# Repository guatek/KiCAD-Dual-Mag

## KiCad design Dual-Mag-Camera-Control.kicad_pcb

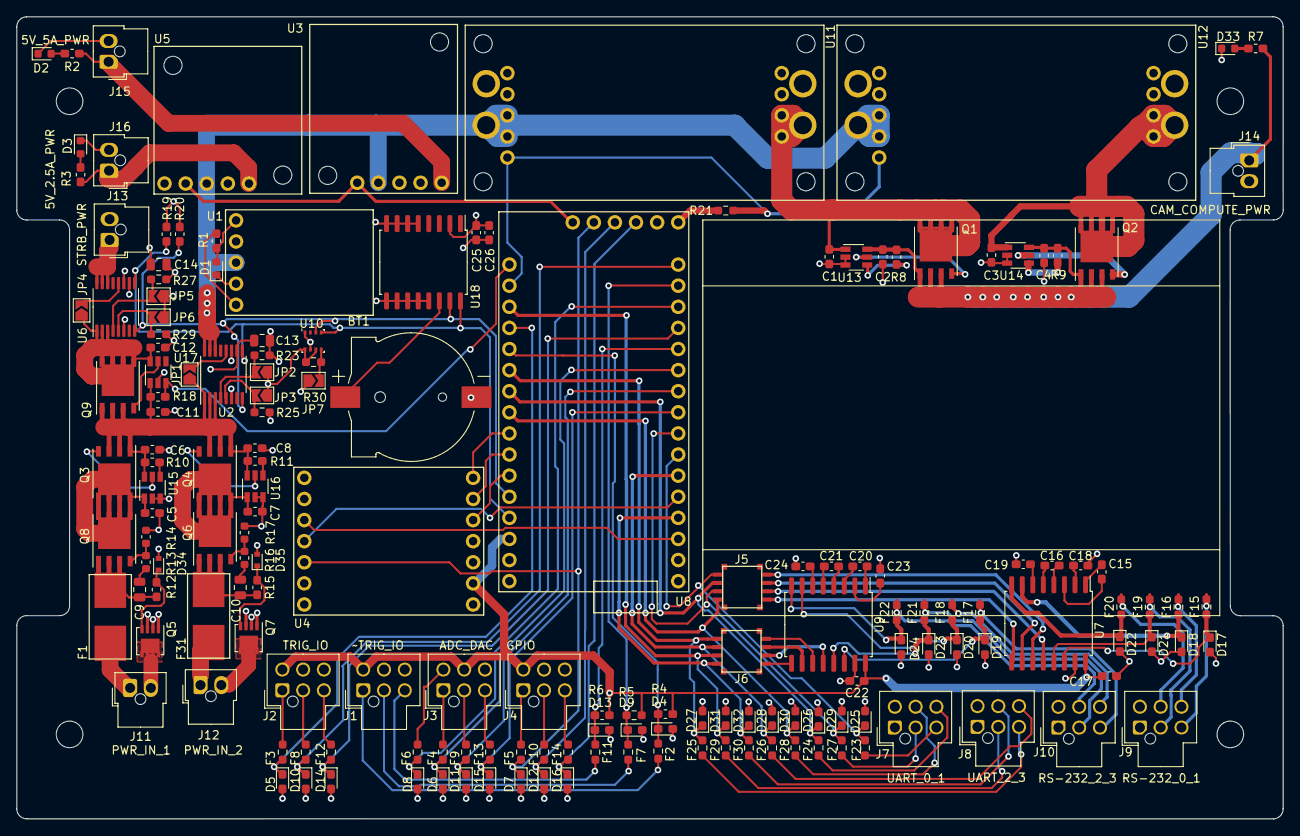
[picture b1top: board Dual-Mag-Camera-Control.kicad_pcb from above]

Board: 4 copper layers, 152.4 x 96.5 mm, 169 parts (0 on the bottom side), 135 nets.

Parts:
BT1: 1056; BAT_1056
C1, C2, C3, C4, C5, C6, C7, C8, C11, C12: 0.1 uF 50V; C_0603_1608Metric_Pad1.05x0.95mm_HandSolder
C9, C10, C13, C14: 1 uF; C_0805_2012Metric
C15, C16, C17, C18, C19, C20, C21, C22, C23, C24, C25: 0.1 uF 50V; C_0603_1608Metric_Pad1.08x0.95mm_HandSolder
C26: 10 uF 50V; C_0603_1608Metric_Pad1.08x0.95mm_HandSolder
D1: GRN 1.7V@1mA; LED_0603_1608Metric
D2, D3, D33: ORG 1.8V@1mA; LED_0603_1608Metric
D4, D5, D6, D7, D8, D9, D10, D11, D12, D13, D14, D15, D16, D25, D26, D27, D28, D29, D30, D31, D32: CZRU52C3V3; D_0603_1608Metric_Pad1.05x0.95mm_HandSolder
D17, D18, D19, D20, D21, D22, D23, D24: CZRU52C15; D_0603_1608Metric_Pad1.05x0.95mm_HandSolder
D34, D35: BZT52C20T-7; D_SOD-523
F1, F31: 01550900M(Holder); 01550900M
F2, F3, F4, F5, F6, F7, F8, F9, F10, F11, F12, F13, F14, F15, F16, F17, F18, F19, F20, F21, F22, F23, F24, F25, F26, F27, F28, F29, F30: PTC; R_0603_1608Metric_Pad0.98x0.95mm_HandSolder
J1: ~TRIG_IO; Molex_Nano-Fit_105310-xx06_2x03_P2.50mm_Vertical
J2: TRIG_IO; Molex_Nano-Fit_105310-xx06_2x03_P2.50mm_Vertical
J3: ADC_DAC; Molex_Nano-Fit_105310-xx06_2x03_P2.50mm_Vertical
J4: GPIO; Molex_Nano-Fit_105310-xx06_2x03_P2.50mm_Vertical
J5, J6: CVS-04TB
J7: UART_0_1; Molex_Nano-Fit_105310-xx06_2x03_P2.50mm_Vertical
J8: UART_2_3; Molex_Nano-Fit_105310-xx06_2x03_P2.50mm_Vertical
J9: RS-232_0_1; Molex_Nano-Fit_105310-xx06_2x03_P2.50mm_Vertical
J10: RS-232_2_3; Molex_Nano-Fit_105310-xx06_2x03_P2.50mm_Vertical
J11: PWR_IN_1; Molex_Nano-Fit_105309-xx02_1x02_P2.50mm_Vertical
J12: PWR_IN_2; Molex_Nano-Fit_105309-xx02_1x02_P2.50mm_Vertical
J13: STRB_PWR; Molex_Nano-Fit_105309-xx02_1x02_P2.50mm_Vertical
J14: CAM_COMPUTE_PWR; Molex_Nano-Fit_105309-xx02_1x02_P2.50mm_Vertical
J15: 5V_5A_PWR; Molex_Nano-Fit_105309-xx02_1x02_P2.50mm_Vertical
J16: 5V_2.5A_PWR; Molex_Nano-Fit_105309-xx02_1x02_P2.50mm_Vertical
JP1, JP2, JP3, JP4, JP5, JP6, JP7: SolderJumper_2_Open; SolderJumper-2_P1.3mm_Open_TrianglePad1.0x1.5mm
Q1, Q2, Q3, Q4, Q6, Q8, Q9: Si7463DP; PowerPAK_SO-8_Single
Q5, Q7: SISS12DN; Vishay_PowerPAK_1212-8_Single
R1, R2, R3: 3240; R_0603_1608Metric_Pad1.05x0.95mm_HandSolder
R4, R6: 1k; R_0603_1608Metric_Pad1.05x0.95mm_HandSolder
R5: 1k; R_0603_1608Metric_Pad0.98x0.95mm_HandSolder
R7: 10.2k; R_0603_1608Metric_Pad1.05x0.95mm_HandSolder
R8, R9, R10, R11, R18: 470k; R_0603_1608Metric_Pad1.05x0.95mm_HandSolder
R12, R15, R19, R20: 10K; R_0603_1608Metric_Pad1.05x0.95mm_HandSolder
R13, R16: 100; R_0603_1608Metric
R14, R17: 499k; R_0603_1608Metric
R21: 20k; R_0603_1608Metric_Pad0.98x0.95mm_HandSolder
R23, R25, R27, R29, R30: 10K; R_0603_1608Metric_Pad0.98x0.95mm_HandSolder
U1: D24V10F5
U2, U6: INA260; TSSOP-16_4.4x5mm_P0.65mm
U3: D24V50F5
U4: LowPowerLab-SD-Card; LowPowerLabs-SD-Card
U5: D24V22F5
U7, U9: SOIC-16W_7.5x10.3mm_P1.27mm
U8: MoteinoM0
U10: BME280; Bosch_LGA-8_2.5x2.5mm_P0.65mm_ClockwisePinNumbering
U11, U12: S18V20F12; S18V20x
U13, U14, U15, U16, U17: LTC4412HVIS6; TSOT-23-6
U18: DS3231M; SOIC-16W_7.5x10.3mm_P1.27mm

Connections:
/3.3V_LDO: C13.1, C14.1, C17.1, C22.1, C25.1, C26.1, J1.4, J2.4, J3.5, J4.4, JP2.1 (A), JP3.1 (A), JP5.1 (A), JP6.1 (A), R4.2, R5.2, R6.2, R19.1, R20.1, R30.1, U2.10 (VS), U4.2 (3V), U6.10 (VS), U7.16 (VCC), U8.30 (3.3V_LDO), U8.34 (3.3V_LDO), U9.16 (VCC), U10.6 (VDDIO), U10.8 (VDD), U18.2 (VCC)
/5V_2.5A_OUT: J16.1, R3.2, U5.1 (Vout)
/5V_5A_OUT: J15.1, R2.2, U3.1 (Out)
/5V_reg: J1.5, J2.5, J4.5, R1.1, U1.5 (Vout), U8.32 (Vin_(3.6V-6V))
/A3: D6.1, F4.1, U8.11 (A3(PA04(AIN4/REFB/SER0:0/TC0:0)))
/A3_IO: F4.2, J3.1
/A4: D11.1, F9.1, U8.10 (A4(PA05(AIN5/SER0:1/TC0:1)))
/A4_IO: F9.2, J3.2
/A5: D15.1, F13.1, U8.9 (A5(PB02(AIN10/SER5:0))
/A5_IO: F13.2, J3.3
/Adafruit_BME280/SDO/ADR: JP7.2 (B), R30.2, U10.5 (SDO)
/Adafruit_INA260/VBUS: JP1.2 (B), U2.12 (VBUS)
/Adafruit_INA260/Vin+: C6.1, C8.1, C11.1, JP1.1 (A), Q3.1 (S), Q3.2 (S), Q3.3 (S), Q4.1 (S), Q4.2 (S), Q4.3 (S), Q9.1 (S), Q9.2 (S), Q9.3 (S), R10.1, R11.1, R18.1, U2.1 (IN+), U2.2 (IN+), U2.3 (IN+), U15.6 (SENSE), U16.6 (SENSE), U17.1 (VIN)
/Adafruit_INA260_1/VBUS: JP4.2 (B), U6.12 (VBUS)
/Adafruit_INA260_1/Vin+: C12.1, JP4.1 (A), Q9.5 (D), U6.1 (IN+), U6.2 (IN+), U6.3 (IN+), U17.6 (SENSE)
/COMMS/RX0: D21.1, F19.1, U7.13 (R1IN)
/COMMS/RX0_OUT: F19.2, J9.2
/COMMS/RX1: D22.1, F20.1, U7.8 (R2IN)
/COMMS/RX1_OUT: F20.2, J9.5
/COMMS/RX2: D23.1, F21.1, U9.13 (R1IN)
/COMMS/RX2_OUT: F21.2, J10.2
/COMMS/RX3: D24.1, F22.1, U9.8 (R2IN)
/COMMS/RX3_OUT: F22.2, J10.5
/COMMS/Sparkfun_MAX3232/R1_OUT: J5.6, U7.12 (R1OUT)
/COMMS/Sparkfun_MAX3232/R2_OUT: J5.5, U7.9 (R2OUT)
/COMMS/Sparkfun_MAX3232/T1_IN: J5.8, U7.11 (T1IN)
/COMMS/Sparkfun_MAX3232/T2_IN: J5.7, U7.10 (T2IN)
/COMMS/Sparkfun_MAX3233/R1_OUT: J6.6, U9.12 (R1OUT)
/COMMS/Sparkfun_MAX3233/R2_OUT: J6.5, U9.9 (R2OUT)
/COMMS/Sparkfun_MAX3233/T1_IN: J6.8, U9.11 (T1IN)
/COMMS/Sparkfun_MAX3233/T2_IN: J6.7, U9.10 (T2IN)
/COMMS/TX0: D17.1, F15.1, U7.14 (T1OUT)
/COMMS/TX0_OUT: F15.2, J9.3
/COMMS/TX1: D18.1, F16.1, U7.7 (T2OUT)
/COMMS/TX1_OUT: F16.2, J9.6
/COMMS/TX2: D19.1, F17.1, U9.14 (T1OUT)
/COMMS/TX2_OUT: F17.2, J10.3
/COMMS/TX3: D20.1, F18.1, U9.7 (T2OUT)
/COMMS/TX3_OUT: F18.2, J10.6
/COMMS/UART_RX0_OUT: F27.2, J7.2
/COMMS/UART_RX1_OUT: F28.2, J7.5
/COMMS/UART_RX2_OUT: F29.2, J8.2
/COMMS/UART_RX3_OUT: F30.2, J8.5
/COMMS/UART_TX0_OUT: F23.2, J7.3
/COMMS/UART_TX1_OUT: F24.2, J7.6
/COMMS/UART_TX2_OUT: F25.2, J8.3
/COMMS/UART_TX3_OUT: F26.2, J8.6
/CamVout: C2.1, C4.1, J14.1, Q1.1 (S), Q1.2 (S), Q1.3 (S), Q2.1 (S), Q2.2 (S), Q2.3 (S), R7.2, R8.1, R9.1, U13.6 (SENSE), U14.6 (SENSE)
/CameraPower/LTC4412HV/Vin: C1.1, Q1.5 (D), U11.4 (Vout), U13.1 (VIN)
/CameraPower/sheet5F4C3746/Vin: C3.1, Q2.5 (D), U12.4 (Vout), U14.1 (VIN)
/DAC_OUT: D8.1, F6.1, U8.14 (A0(PA02(AIN0/DAC)))
/DAC_OUT_IO: F6.2, J3.4
/GND: BT1.-, C1.2, C2.2, C3.2, C4.2, C5.2, C6.2, C7.2, C8.2, C11.2, C12.2, C13.2, C14.2, C17.2, C18.2, C19.2, C22.2, C23.2, C24.2, C25.2, C26.2, D1.1 (K), D2.1 (K), D3.1 (K), D4.2, D5.2, D6.2, D7.2, D8.2, D9.2, D10.2, D11.2, D12.2, D13.2, D14.2, D15.2, D16.2, D17.2, D18.2, D19.2, D20.2, D21.2, D22.2, D23.2, D24.2, D25.2, D26.2, D27.2, D28.2, D29.2, D30.2, D31.2, D32.2, D33.1 (K), D34.2 (A), D35.2 (A), J1.6, J2.6, J3.6, J4.6, J7.1, J7.4, J8.1, J8.4, J9.1, J9.4, J10.1, J10.4, J13.2, J14.2, J15.2, J16.2, JP7.1 (A), Q5.1 (S), Q5.2 (S), Q5.3 (S), Q7.1 (S), Q7.2 (S), Q7.3 (S), R14.2, R17.2, R21.2, R23.2, R25.2, R27.2, R29.2, U1.4 (GND), U2.6 (GND), U2.11 (GND), U3.2 (GND), U3.3 (GND), U4.1 (GND), U4.14 (GND), U5.2 (GND), U6.6 (GND), U6.11 (GND), U7.15 (GND), U8.2 (GND), U8.31 (GND), U8.33 (GND), U9.15 (GND), U10.1 (GND), U10.7 (GND), U11.1 (GND), U11.5 (GND), U12.1 (GND), U12.5 (GND), U13.2 (GND), U13.3 (CTL), U14.2 (GND), U14.3 (CTL), U15.2 (GND), U15.3 (CTL), U16.2 (GND), U16.3 (CTL), U17.2 (GND), U18.5 (GND), U18.6 (GND), U18.7 (GND), U18.8 (GND), U18.9 (GND), U18.10 (GND), U18.11 (GND), U18.12 (GND), U18.13 (GND)
/GPIO_1: D7.1, F5.1, U4.12 (CD), U8.37 (AREF(PA03(AIN1/REFA)))
/GPIO_1_IO: F5.2, J4.1
/GPIO_2: D12.1, F10.1, U8.36 (SWDIO(PA31(SWDIO/SER1:3+)))
/GPIO_2_IO: F10.2, J4.2
/GPIO_3: D16.1, F14.1, U8.35 (SWCLK(PA30(SWCLK/SER1:2+)))
/GPIO_3_IO: F14.2, J4.3
/PowerInput1/Vin: C5.1, Q3.5 (D), Q8.5 (D), U15.1 (VIN)
/PowerInput2/Vin: C7.1, Q4.5 (D), Q6.5 (D), U16.1 (VIN)
/PowerInputPreotection2/Vin: F31.1, J12.1
/PowerInputProtection/Vin: F1.1, J11.1
/SCL_1: R19.2, U2.9 (SCL), U6.9 (SCL), U8.29 (SCL(PA23(I2C/SER3:0+))), U10.4 (SCK), U18.16 (SCL)
/SDA_1: R20.2, U2.8 (SDA), U6.8 (SDA), U8.28 (SDA(PA22(I2C/SER3:0+))), U10.3 (SDI), U18.15 (SDA)
/SD_CS: U4.10 (CS), U8.3 (D13(PA17(I2C/SER1:1+)))
/SD_ENABLE: U4.11 (EN), U8.5 (D11(PA16(I2C/SER1:0+)))
/SPI_MISO: U4.5 (MI), U8.27 (SPI_MISO(PA12(I2C/SER2:0+)))
/SPI_MOSI: U4.7 (MO), U8.25 (SPI_MOSI(PB10(SER4:2+)))
/SPI_SCK: U4.6 (SCK), U8.26 (SPI_SCK(PB11(SER4:3+)))
/Serial0_RX: D29.1, F27.1, J5.3, U8.8 (D31(PB23(SER5:3+)))
/Serial0_TX: D25.1, F23.1, J5.1, U8.7 (D30(PB22(SER5:2+)))
/Serial1_RX: D30.1, F28.1, J5.4, U8.24 (D0(PA11(AIN19/SER0:3+)))
/Serial1_TX: D26.1, F24.1, J5.2, U8.23 (D1(PA10(AIN18/SER0:2+)))
/Serial2_RX: D31.1, F29.1, J6.3, U8.19 (D5(PA15(XOUT/SER2:3+)))
/Serial2_TX: D27.1, F25.1, J6.1, U8.22 (D2(PA14(XIN/SER2:2+)))
/Serial3_RX: D32.1, F30.1, J6.4, U8.4 (D12(PA19(SER1:3+)))
/Serial3_TX: D28.1, F26.1, J6.2, U8.6 (D10(PA18(SER1:2+)))
/StrobeVout: J13.1, U6.14 (IN-), U6.15 (IN-), U6.16 (IN-)
/SystemVin: U1.3 (Vin), U2.14 (IN-), U2.15 (IN-), U2.16 (IN-), U3.4 (Vin), U5.3 (Vin), U11.2 (Vin), U12.2 (Vin)
/TRIG0_0: D5.1, F3.1, U8.20 (D4(PA08(I2C/AIN16/SER0:0+)))
/TRIG0_0_IO: F3.2, J2.1
/TRIG0_1: D4.1, F2.1, R4.1, U8.21 (D3(PA09(I2C/AIN17/SER0:1+)))
/TRIG0_1_IO: F2.2, J1.1
/TRIG1_0: D10.1, F8.1, U8.16 (D8(PA06/AIN6/SER0:2/TC1:0))
/TRIG1_0_IO: F8.2, J2.2
/TRIG1_1: D9.1, F7.1, R5.1, U8.15 (D9(PA07/AIN7/SER0:3/TC1:1)))
/TRIG1_1_IO: F7.2, J1.2
/TRIG4_0: D14.1, F12.1, U8.13 (A1(PB08(AIN2/SER4:0/TC4:0)))
/TRIG4_0_IO: F12.2, J2.3
/TRIG4_1: D13.1, F11.1, R6.1, U8.12 (A2(PB09(AIN3/SER4:1/TC4:1)))
/TRIG4_1_IO: F11.2, J1.3
/uGnd1: J11.2, Q5.5 (D)
/uGnd2: J12.2, Q7.5 (D)
/~5V_ENABLE: U3.5 (EN), U5.4 (EN), U8.38 (ANT(PA13(I2C/SER2:1+)))
/~12V_ENABLE: R21.1, U8.18 (D6(PA20(SER5:2+))), U11.3 (ENABLE), U12.3 (ENABLE)
/~STROBE_ENABLE: R18.2, U8.17 (D7(PA21(SER5:3+))), U17.3 (CTL)
unnamed: BT1.+, U18.14 (VBAT)
unnamed: C9.1, F1.2, Q8.1 (S), Q8.2 (S), Q8.3 (S), R12.1
unnamed: C9.2, R13.2
unnamed: C10.1, F31.2, Q6.1 (S), Q6.2 (S), Q6.3 (S), R15.1
unnamed: C10.2, R16.2
unnamed: C15.1, U7.3 (C1-)
unnamed: C15.2, U7.1 (C1+)
unnamed: C16.1, U7.4 (C2+)
unnamed: C16.2, U7.5 (C2-)
unnamed: C18.1, U7.2 (VS+)
unnamed: C19.1, U7.6 (VS-)
unnamed: C20.1, U9.3 (C1-)
unnamed: C20.2, U9.1 (C1+)
unnamed: C21.1, U9.4 (C2+)
unnamed: C21.2, U9.5 (C2-)
unnamed: C23.1, U9.2 (VS+)
unnamed: C24.1, U9.6 (VS-)
unnamed: D1.2 (A), R1.2, U1.1 (PG)
unnamed: D2.2 (A), R2.1
unnamed: D3.2 (A), R3.1
unnamed: D33.2 (A), R7.1
unnamed: D34.1 (K), Q5.4 (G), R12.2
unnamed: D35.1 (K), Q7.4 (G), R15.2
unnamed: JP2.2 (B), R23.1, U2.4 (A1)
unnamed: JP3.2 (B), R25.1, U2.5 (A0)
unnamed: JP5.2 (B), R27.1, U6.4 (A1)
unnamed: JP6.2 (B), R29.1, U6.5 (A0)
unnamed: Q1.4 (G), U13.5 (GATE)
unnamed: Q2.4 (G), U14.5 (GATE)
unnamed: Q3.4 (G), U15.5 (GATE)
unnamed: Q4.4 (G), U16.5 (GATE)
unnamed: Q6.4 (G), R16.1, R17.1
unnamed: Q8.4 (G), R13.1, R14.1
unnamed: Q9.4 (G), U17.5 (GATE)
unnamed: R8.2, U13.4 (STAT)
unnamed: R9.2, U14.4 (STAT)
unnamed: R10.2, U15.4 (STAT)
unnamed: R11.2, U16.4 (STAT)

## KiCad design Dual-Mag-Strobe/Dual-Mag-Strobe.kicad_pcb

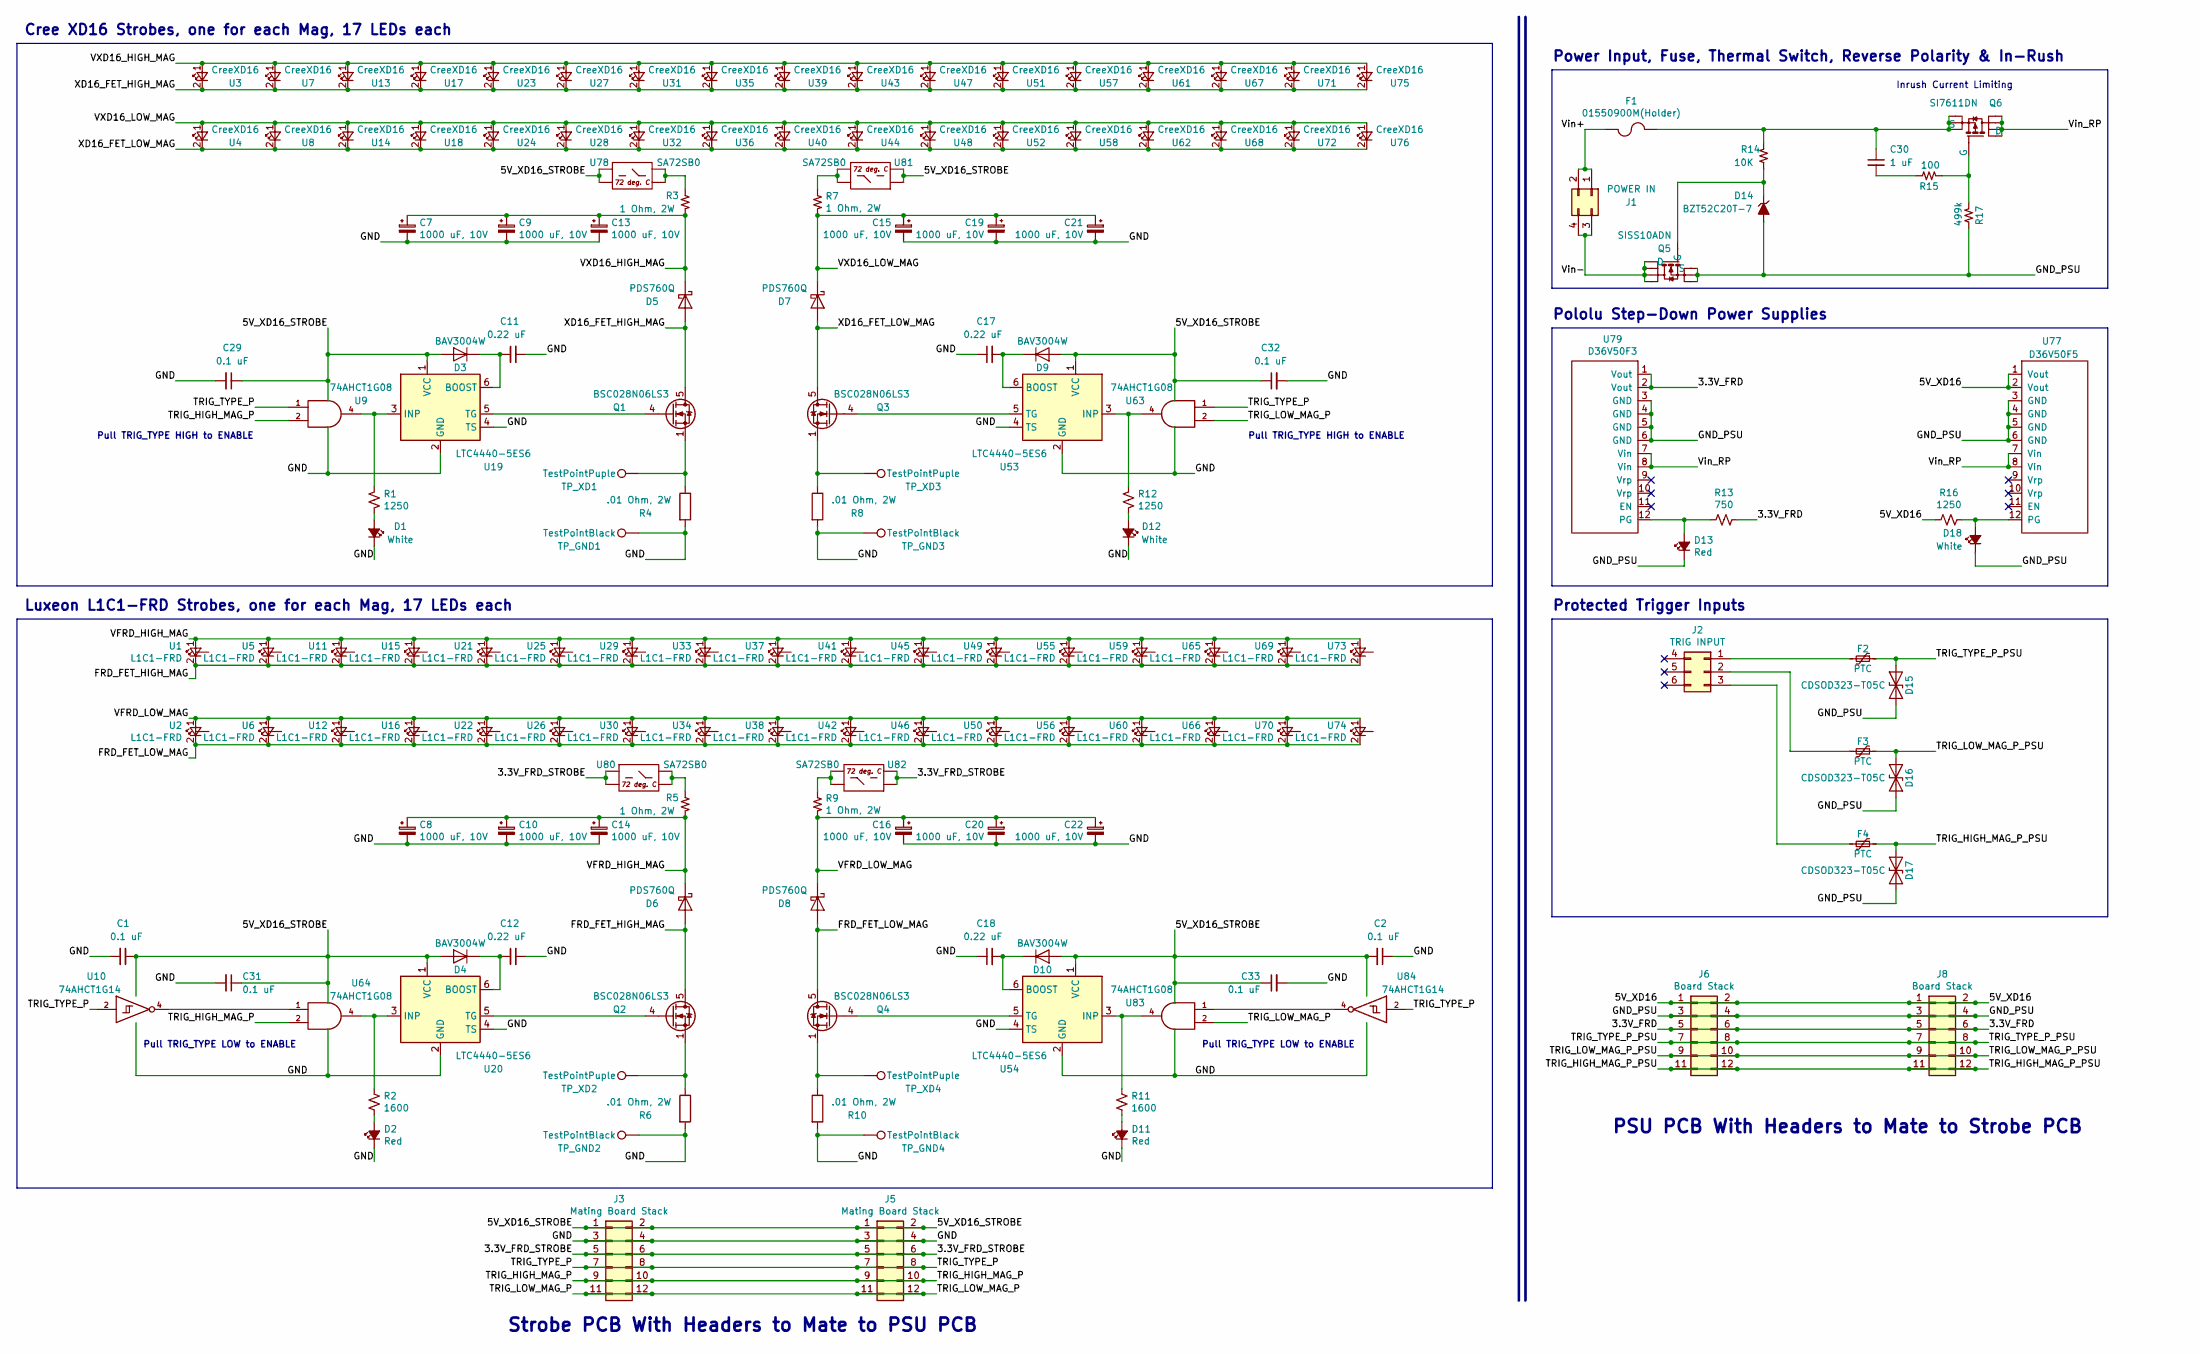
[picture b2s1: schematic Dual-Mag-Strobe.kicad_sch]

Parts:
C1, C2, C29, C31, C32, C33: 0.1 uF; C_0603_1608Metric; Part Number 399-7845-1-ND
C7, C8, C9, C10, C13, C14, C15, C16, C19, C20, C21, C22: 1000 uF, 10V; CP_EIA-7360-38_Kemet-E; Part Number 399-18694-1-ND
C11, C12, C17, C18: 0.22 uF; C_0603_1608Metric; Part Number 490-14410-1-ND
C30: 1 uF; C_0805_2012Metric; Part Number 311-3498-1-ND
D1, D12, D18: White; LED_0603_1608Metric; Part Number 1080-1574-1-ND
D2, D11, D13: Red; LED_0603_1608Metric; Part Number 475-2506-1-ND
D3, D4, D9, D10: BAV3004W; D_SOD-123; Part Number BAV3004W-FDICT-ND
D5, D6, D7, D8: PDS760Q; D_PowerDI-5; Part Number PDS760Q-13DICT-ND
D14: BZT52C20T-7; D_SOD-523; Part Number BZT52C20T-7
D15, D16, D17: CDSOD323-T05C; D_SOD-323; Part Number CDSOD323-T05CCT-ND
F1: 01550900M(Holder); 01550900M; Part Number F1889-ND
F2, F3, F4: PTC; R_1210_3225Metric; Part Number 495-3878-1-ND
J1: POWER IN; Molex_Nano-Fit_105310-xx04_2x02_P2.50mm_Vertical; Part Number WM15166-ND
J2: TRIG INPUT; Molex_Nano-Fit_105310-xx06_2x03_P2.50mm_Vertical; Part Number WM15076-ND
J3, J5: Mating Board Stack; PinSocket_2x06_P2.54mm_Vertical; Part Number SAM1092-06-ND
J6, J8: Board Stack; PinHeader_2x06_P2.54mm_Vertical; Part Number SAM1022-06-ND
Q1, Q2, Q3, Q4: BSC028N06LS3; TDSON-8-1; Part Number BSC028N06LS3GATMA1CT-ND
Q5: SISS10ADN; Vishay_PowerPAK_1212-8_Single; Part Number SISS10ADN-T1-GE3
Q6: SI7611DN; Vishay_PowerPAK_1212-8_Single; Part Number SI7611DN-T1-GE3
R1, R12, R16: 1250; R_0603_1608Metric; Part Number P1.27KHCT-ND
R2, R11: 1600; R_0603_1608Metric; Part Number P1.60KHCT-ND
R3, R5, R7, R9: 1 Ohm, 2W; R_2512_6332Metric; Part Number CRM2512-FX-1R00ELFCT-ND
R4, R6, R8, R10: .01 Ohm, 2W; R_2512_6332Metric; Part Number RHM.010AUCT-ND
R13: 750; R_0603_1608Metric; Part Number P750BYCT-ND
R14: 10K; R_0603_1608Metric_Pad1.05x0.95mm_HandSolder; Part Number MCT0603-10.0K-CFCT-ND
R15: 100; R_0603_1608Metric; Part Number P100DBCT-ND
R17: 499k; R_0603_1608Metric; Part Number YAG4565CT-ND
TP_GND1, TP_GND2, TP_GND3, TP_GND4: TestPointBlack; TestPoint_519xTR; Part Number 36-5191CT-ND
TP_XD1, TP_XD2, TP_XD3, TP_XD4: TestPointPuple; TestPoint_519xTR; Part Number 36-5199CT-ND
U1, U2, U5, U6, U11, U12, U15, U16, U21, U22, U25, U26, U29, U30, U33, U34, U37, U38, U41, U42, U45, U46, U49, U50, U55, U56, U59, U60, U65, U66, U69, U70, U73, U74: L1C1-FRD; Luxeon-L1C1-FRD; Part Number 997-L1C1-FRD10000000
U3, U4, U7, U8, U13, U14, U17, U18, U23, U24, U27, U28, U31, U32, U35, U36, U39, U40, U43, U44, U47, U48, U51, U52, U57, U58, U61, U62, U67, U68, U71, U72, U75, U76: CreeXD16; Cree_XD16_Min; Part Number 941-XD16AWTH000KE4
U9, U63, U64, U83: 74AHCT1G08; SOT-23-5; Part Number 296-1113-1-ND
U10, U84: 74AHCT1G14; SOT-23-5; Part Number 296-1112-1-ND
U19, U20, U53, U54: LTC4440-5ES6; SOT-23-6
U77: D36V50F5; D36V50Fx; Part Number 2183-4091-ND
U78, U80, U81, U82: SA72SB0; Part Number SA72SB0CT-ND
U79: D36V50F3; D36V50Fx; Part Number 2183-4090-ND

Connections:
/3.3V_FRD: J6.5, J6.6, J8.5, J8.6, R13.2, U79.1 (Vout), U79.2 (Vout)
/3.3V_FRD_STROBE: J3.5, J3.6, J5.5, J5.6, U80.1, U80.2, U82.1, U82.2
/5V_XD16: J6.1, J6.2, J8.1, J8.2, R16.1, U77.1 (Vout), U77.2 (Vout)
/FRD_FET_HIGH_MAG: D6.2 (A), Q2.5 (D), U1.2 (K), U5.2 (K), U11.2 (K), U15.2 (K), U21.2 (K), U25.2 (K), U29.2 (K), U33.2 (K), U37.2 (K), U41.2 (K), U45.2 (K), U49.2 (K), U55.2 (K), U59.2 (K), U65.2 (K), U69.2 (K), U73.2 (K)
/FRD_FET_LOW_MAG: D8.2 (A), Q4.5 (D), U2.2 (K), U6.2 (K), U12.2 (K), U16.2 (K), U22.2 (K), U26.2 (K), U30.2 (K), U34.2 (K), U38.2 (K), U42.2 (K), U46.2 (K), U50.2 (K), U56.2 (K), U60.2 (K), U66.2 (K), U70.2 (K), U74.2 (K)
/GND_PSU: D13.1 (K), D14.2 (A), D15.2 (A2), D16.2 (A2), D17.2 (A2), D18.1 (K), J6.3, J6.4, J8.3, J8.4, Q5.1 (S), Q5.2 (S), Q5.3 (S), R17.2, U77.3 (GND), U77.4 (GND), U77.5 (GND), U77.6 (GND), U79.3 (GND), U79.4 (GND), U79.5 (GND), U79.6 (GND)
/TRIG_HIGH_MAG_P: J3.9, J3.10, J5.9, J5.10, U9.2, U64.2
/TRIG_HIGH_MAG_P_PSU: D17.1 (A1), F4.1, J6.11, J6.12, J8.11, J8.12
/TRIG_LOW_MAG_P: J3.11, J3.12, J5.11, J5.12, U63.2, U83.2
/TRIG_LOW_MAG_P_PSU: D16.1 (A1), F3.1, J6.9, J6.10, J8.9, J8.10
/TRIG_TYPE_P: J3.7, J3.8, J5.7, J5.8, U9.1, U10.2, U63.1, U84.2
/TRIG_TYPE_P_PSU: D15.1 (A1), F2.1, J6.7, J6.8, J8.7, J8.8
/VFRD_HIGH_MAG: C8.1, C10.1, C14.1, D6.1 (K), R5.1, U1.1 (A), U5.1 (A), U11.1 (A), U15.1 (A), U21.1 (A), U25.1 (A), U29.1 (A), U33.1 (A), U37.1 (A), U41.1 (A), U45.1 (A), U49.1 (A), U55.1 (A), U59.1 (A), U65.1 (A), U69.1 (A), U73.1 (A)
/VFRD_LOW_MAG: C16.1, C20.1, C22.1, D8.1 (K), R9.1, U2.1 (A), U6.1 (A), U12.1 (A), U16.1 (A), U22.1 (A), U26.1 (A), U30.1 (A), U34.1 (A), U38.1 (A), U42.1 (A), U46.1 (A), U50.1 (A), U56.1 (A), U60.1 (A), U66.1 (A), U70.1 (A), U74.1 (A)
/VXD16_HIGH_MAG: C7.1, C9.1, C13.1, D5.1 (K), R3.1, U3.1 (A), U7.1 (A), U13.1 (A), U17.1 (A), U23.1 (A), U27.1 (A), U31.1 (A), U35.1 (A), U39.1 (A), U43.1 (A), U47.1 (A), U51.1 (A), U57.1 (A), U61.1 (A), U67.1 (A), U71.1 (A), U75.1 (A)
/VXD16_LOW_MAG: C15.1, C19.1, C21.1, D7.1 (K), R7.1, U4.1 (A), U8.1 (A), U14.1 (A), U18.1 (A), U24.1 (A), U28.1 (A), U32.1 (A), U36.1 (A), U40.1 (A), U44.1 (A), U48.1 (A), U52.1 (A), U58.1 (A), U62.1 (A), U68.1 (A), U72.1 (A), U76.1 (A)
/Vin+: F1.1, J1.1, J1.2
/Vin-: J1.3, J1.4, Q5.5 (D)
/Vin_RP: Q6.5 (D), U77.7 (Vin), U77.8 (Vin), U79.7 (Vin), U79.8 (Vin)
/XD16_FET_HIGH_MAG: D5.2 (A), Q1.5 (D), U3.2 (K), U7.2 (K), U13.2 (K), U17.2 (K), U23.2 (K), U27.2 (K), U31.2 (K), U35.2 (K), U39.2 (K), U43.2 (K), U47.2 (K), U51.2 (K), U57.2 (K), U61.2 (K), U67.2 (K), U71.2 (K), U75.2 (K)
/XD16_FET_LOW_MAG: D7.2 (A), Q3.5 (D), U4.2 (K), U8.2 (K), U14.2 (K), U18.2 (K), U24.2 (K), U28.2 (K), U32.2 (K), U36.2 (K), U40.2 (K), U44.2 (K), U48.2 (K), U52.2 (K), U58.2 (K), U62.2 (K), U68.2 (K), U72.2 (K), U76.2 (K)
GND: C1.2, C2.1, C7.2, C8.2, C9.2, C10.2, C11.2, C12.2, C13.2, C14.2, C15.2, C16.2, C17.1, C18.1, C19.2, C20.2, C21.2, C22.2, C29.2, C31.2, C32.2, C33.2, D1.1 (K), D2.1 (K), D11.1 (K), D12.1 (K), J3.3, J3.4, J5.3, J5.4, R4.2, R6.2, R8.2, R10.2, TP_GND1.1, TP_GND2.1, TP_GND3.1, TP_GND4.1, U9.3 (GND), U10.3 (GND), U19.2 (GND), U19.4 (TS), U20.2 (GND), U20.4 (TS), U53.2 (GND), U53.4 (TS), U54.2 (GND), U54.4 (TS), U63.3 (GND), U64.3 (GND), U83.3 (GND), U84.3 (GND)
unnamed: C11.1, D3.1 (K), U19.6 (BOOST)
unnamed: C12.1, D4.1 (K), U20.6 (BOOST)
unnamed: C17.2, D9.1 (K), U53.6 (BOOST)
unnamed: C18.2, D10.1 (K), U54.6 (BOOST)
unnamed: C30.1, F1.2, Q6.1 (S), Q6.2 (S), Q6.3 (S), R14.1
unnamed: C30.2, R15.2
unnamed: D1.2 (A), R1.2
unnamed: D2.2 (A), R2.2
unnamed: D11.2 (A), R11.2
unnamed: D12.2 (A), R12.2
unnamed: D13.2 (A), R13.1, U79.12 (PG)
unnamed: D14.1 (K), Q5.4 (G), R14.2
unnamed: D18.2 (A), R16.2, U77.12 (PG)
unnamed: F2.2, J2.1
unnamed: F3.2, J2.2
unnamed: F4.2, J2.3
unnamed: Q1.1 (S), Q1.2 (S), Q1.3 (S), R4.1, TP_XD1.1
unnamed: Q1.4 (G), U19.5 (TG)
unnamed: Q2.1 (S), Q2.2 (S), Q2.3 (S), R6.1, TP_XD2.1
unnamed: Q2.4 (G), U20.5 (TG)
unnamed: Q3.1 (S), Q3.2 (S), Q3.3 (S), R8.1, TP_XD3.1
unnamed: Q3.4 (G), U53.5 (TG)
unnamed: Q4.1 (S), Q4.2 (S), Q4.3 (S), R10.1, TP_XD4.1
unnamed: Q4.4 (G), U54.5 (TG)
unnamed: Q6.4 (G), R15.1, R17.1
unnamed: R1.1, U9.4, U19.3 (INP)
unnamed: R2.1, U20.3 (INP), U64.4
unnamed: R3.2, U78.3, U78.4
unnamed: R5.2, U80.3, U80.4
unnamed: R7.2, U81.3, U81.4
unnamed: R9.2, U82.3, U82.4
unnamed: R11.1, U54.3 (INP), U83.4
unnamed: R12.1, U53.3 (INP), U63.4
unnamed: U10.4, U64.1
unnamed: U83.1, U84.4
VCC: C1.1, C2.2, C29.1, C31.1, C32.1, C33.1, D3.2 (A), D4.2 (A), D9.2 (A), D10.2 (A), J3.1, J3.2, J5.1, J5.2, U9.5 (VCC), U10.5 (VCC), U19.1 (VCC), U20.1 (VCC), U53.1 (VCC), U54.1 (VCC), U63.5 (VCC), U64.5 (VCC), U78.1, U78.2, U81.1, U81.2, U83.5 (VCC), U84.5 (VCC)

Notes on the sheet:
Luxeon L1C1-FRD Strobes, one for each Mag, 17 LEDs each
Pull TRIG_TYPE HIGH to ENABLE
Inrush Current Limiting
Power Input, Fuse, Thermal Switch, Reverse Polarity & In-Rush
Pull TRIG_TYPE LOW to ENABLE
Pololu Step-Down Power Supplies
PSU PCB With Headers to Mate to Strobe PCB
Strobe PCB With Headers to Mate to PSU PCB
Cree XD16 Strobes, one for each Mag, 17 LEDs each
Protected Trigger Inputs

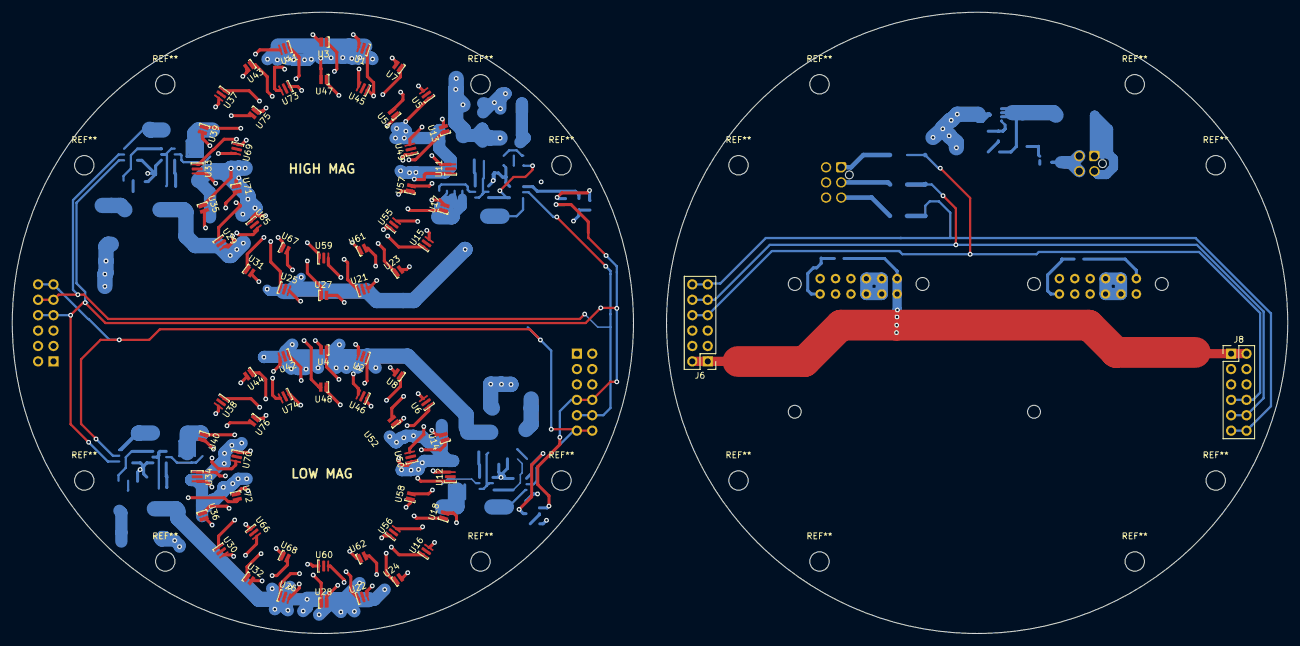
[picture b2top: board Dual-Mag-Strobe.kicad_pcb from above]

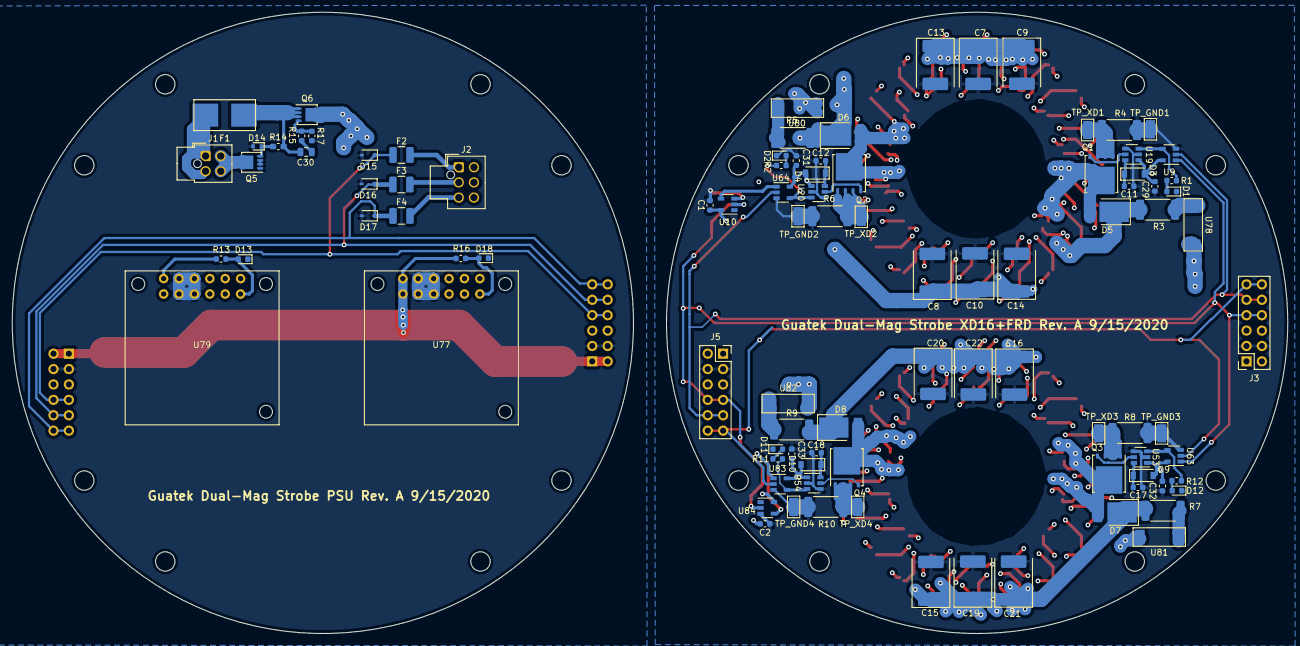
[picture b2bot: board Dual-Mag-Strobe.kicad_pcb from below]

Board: 4 copper layers, 102.5 x 102.5 mm, 166 parts (96 on the bottom side), 58 nets.

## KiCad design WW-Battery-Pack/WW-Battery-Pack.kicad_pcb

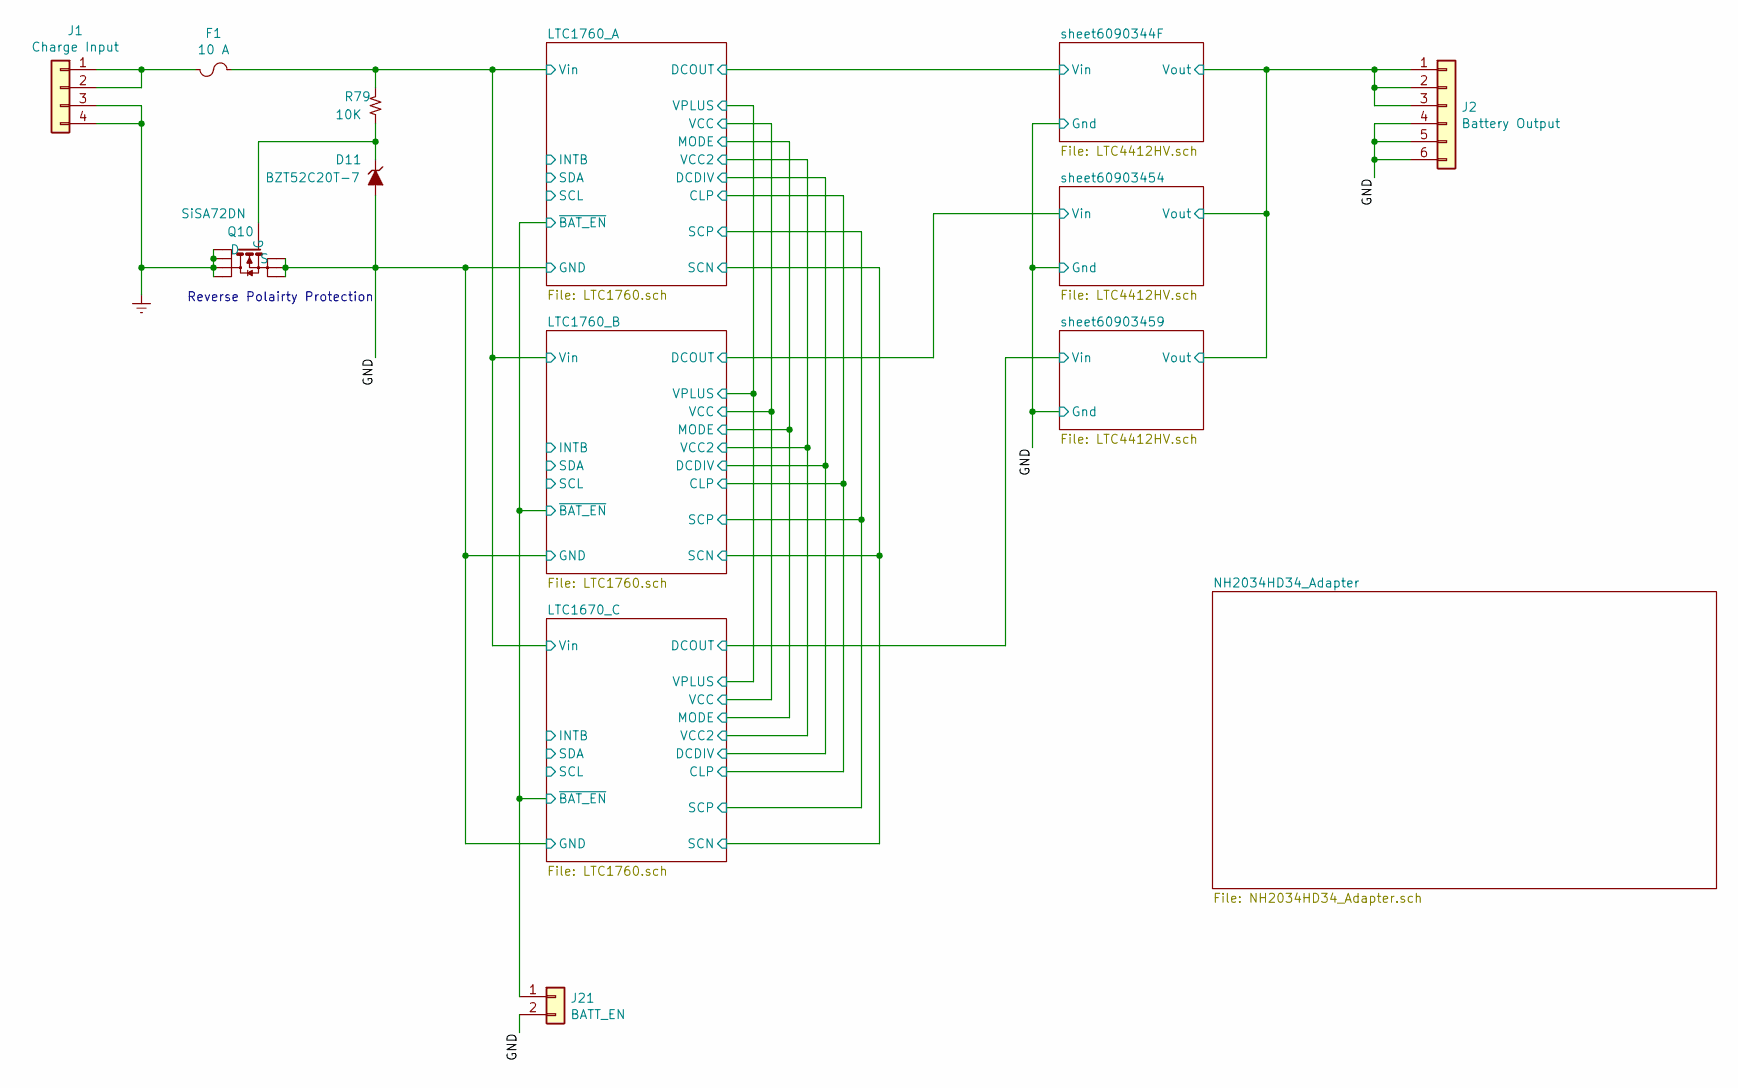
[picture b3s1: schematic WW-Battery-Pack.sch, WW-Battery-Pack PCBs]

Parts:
D11: BZT52C20T-7; D_SOD-523; Part Number BZT52C20T-7
F1: 10 A; 01550900M; Part Number F1889-ND
J1: Charge Input; Molex_Mini-Fit_Jr_5566-04A_2x02_P4.20mm_Vertical; Part Number WM23801-ND
J2: Battery Output; Molex_Mini-Fit_Jr_5566-06A_2x03_P4.20mm_Vertical; Part Number WM3802-ND
J21: BATT_EN; PinHeader_1x02_P2.54mm_Vertical
Q10: SiSA72DN; PowerPAK 1212; Part Number SISA72DN-T1-GE3CT-ND
R79: 10K; R_0603_1608Metric_Pad1.05x0.95mm_HandSolder; Part Number MCT0603-10.0K-CFCT-ND

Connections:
/GND: D11.2 (A), J2.4, J2.5, J2.6, J21.2, Q10.1 (S), Q10.2 (S), Q10.3 (S); also elsewhere on the board
/LTC1670_C/Vin: F1.2, R79.1; also elsewhere on the board
/LTC1670_C/~BAT_EN: J21.1; also elsewhere on the board
/sheet6090344F/Vout: J2.1, J2.2, J2.3; also elsewhere on the board
GNDREF: J1.3, J1.4, Q10.5 (D)
unnamed: D11.1 (K), Q10.4 (G), R79.2
unnamed: F1.1, J1.1, J1.2

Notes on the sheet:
Reverse Polairty Protection
